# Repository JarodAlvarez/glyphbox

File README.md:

# GLYPHBOX

A 1-bit fantasy console you can build yourself. Games are written in Lua, printed as Aztec codes on credit-card-sized cards, and read by a camera in the console's card slot.

| | |
|---|---|
| Display | 128 × 128, 1-bit |
| Input | D-pad, action button, menu button |
| Audio | 2 cart channels (square, triangle, noise) + system channel |
| Sprites | 128 tiles, 8 × 8, 1-bit |
| Frame rate | 30 fps |
| Carts | Lua, up to 8 cards |

**Website:** https://jarodalvarez.github.io/glyphbox/

**Try it:** the [browser playground](https://jarodalvarez.github.io/glyphbox/playground/) runs the real console in your browser. Write Lua, draw sprites, and run.

**Learn:** [make your first game](https://jarodalvarez.github.io/glyphbox/learn/) in six lessons, with every example running on a live console. The [docs](docs/) cover the full API and the card budget.

**Make a game:** install the [devkit](devkit/) for `glyph new`, `glyph run` (live reload), `glyph build` and `glyph print`.

| Folder | What's in it |
|---|---|
| [docs/](docs/) | Lessons, API reference, cart format |
| [devkit/](devkit/) | The `glyph` command-line devkit |
| [games/](games/) | Original games, with source |
| [hardware/](hardware/) | Bill of materials. Case and controller files are coming |
| [site/](site/) | The website and playground |

## Licenses

GLYPHBOX is several things under different terms. See [LICENSE.md](LICENSE.md).

- **Devkit and example code:** MIT
- **Docs:** CC BY 4.0
- **Hardware files:** CC BY-NC-SA 4.0. Build one, modify it and share it, but don't sell it.
- **Console software:** proprietary, free to download and use
- **Name and logo:** see [TRADEMARK.md](TRADEMARK.md)

Games you make belong to you. License them however you like.

(C) Gureedo 2026

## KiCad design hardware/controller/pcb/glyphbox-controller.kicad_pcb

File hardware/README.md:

# Hardware

Everything needed to build a GLYPHBOX console and its controller. The [build guide](https://jarodalvarez.github.io/glyphbox/docs/build.html) walks through it step by step.

| Folder | What's in it |
|---|---|
| [BOM.csv](BOM.csv) | Every part, with quantities and notes |
| [case/](case/) | The console case: STLs to print, and the parametric script that makes them |
| [controller/pcb/](controller/pcb/) | The controller board: KiCad project, footprints, 3D model and Gerbers ready to order |
| [controller/firmware/](controller/firmware/) | `code.py` for the Raspberry Pi Pico (CircuitPython) |
| [controller/shell/](controller/shell/) | The printed controller shell, and the scripts that build it |

**One part you add yourself:** the controller shell's membrane mounts come from the Lensless Game Boy Pocket shell, whose licence doesn't allow sharing adaptations. The shell here is published without them, and [controller/shell/](controller/shell/) shows how to add them from your own download.

## Licence

The hardware files are licensed **CC BY-NC-SA 4.0**. You can build, modify and share them, but not sell consoles, kits or parts made from them, and changes you share must use the same licence. The GLYPHBOX name and logo are covered separately, see [TRADEMARK.md](../TRADEMARK.md).

## Credits

- The controller's membrane pad shapes are adapted from Natalie the Nerd's [YAPoco](https://github.com/nataliethenerd) Game Boy Pocket reference.
- The controller shell's membrane mounts come from the [Lensless Gameboy Pocket / Pocket Color Shell](http://pcbway.com/project/shareproject/Lensless_Gameboy_Pocket_Pocket_Color_Shell_243a0f87.html) (CC BY-NC-ND), added by each builder from their own copy.
- The controller uses reproduction Game Boy Pocket buttons and membranes.

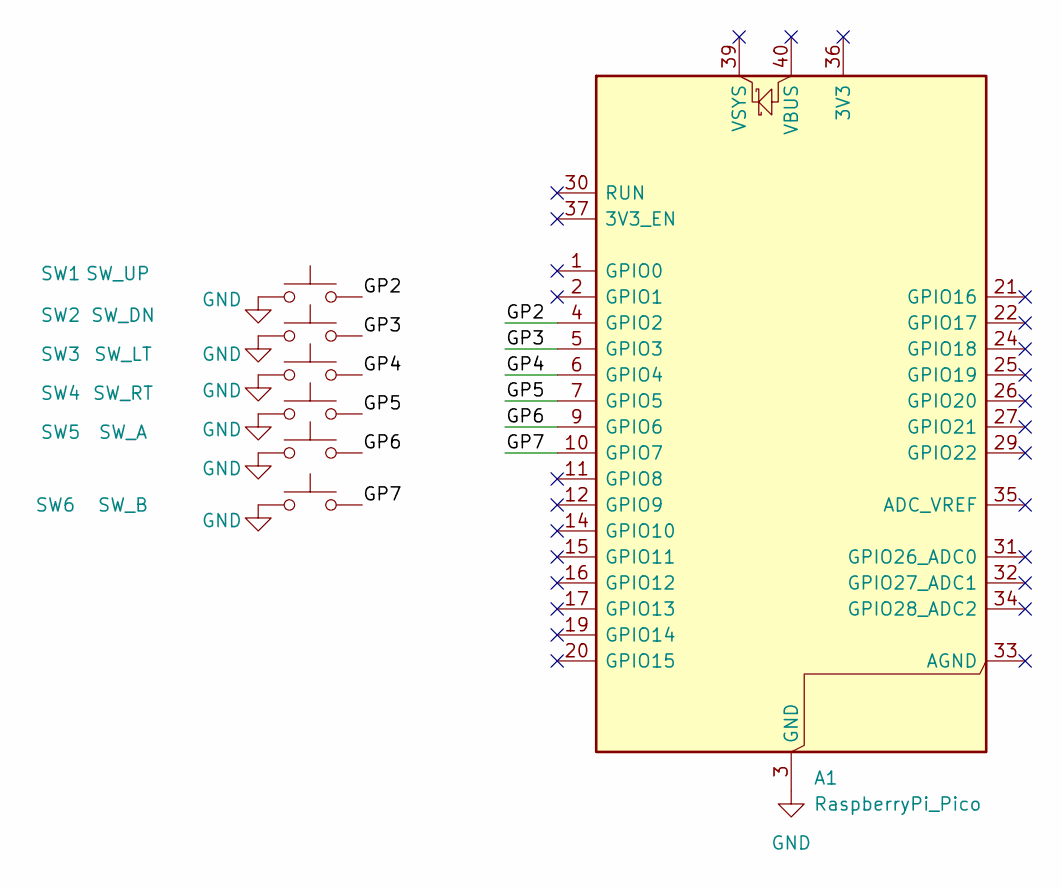
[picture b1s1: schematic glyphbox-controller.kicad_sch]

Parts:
A1: RaspberryPi_Pico; RaspberryPi_Pico_Common_Unspecified
SW1: SW_UP; GBP_Membrane_Contact
SW2: SW_DN; GBP_Membrane_Contact
SW3: SW_LT; GBP_Membrane_Contact
SW4: SW_RT; GBP_Membrane_Contact
SW5: SW_A; GBP_Membrane_Contact
SW6: SW_B; GBP_Membrane_Contact_CGB

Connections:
/GP2: A1.4 (GPIO2), SW1.2
/GP3: A1.5 (GPIO3), SW2.2
/GP4: A1.6 (GPIO4), SW3.2
/GP5: A1.7 (GPIO5), SW4.2
/GP6: A1.9 (GPIO6), SW5.2
/GP7: A1.10 (GPIO7), SW6.2
GND: A1.3 (GND), A1.8 (GND), A1.13 (GND), A1.18 (GND), A1.23 (GND), A1.28 (GND), A1.38 (GND), SW1.1, SW2.1, SW3.1, SW4.1, SW5.1, SW6.1

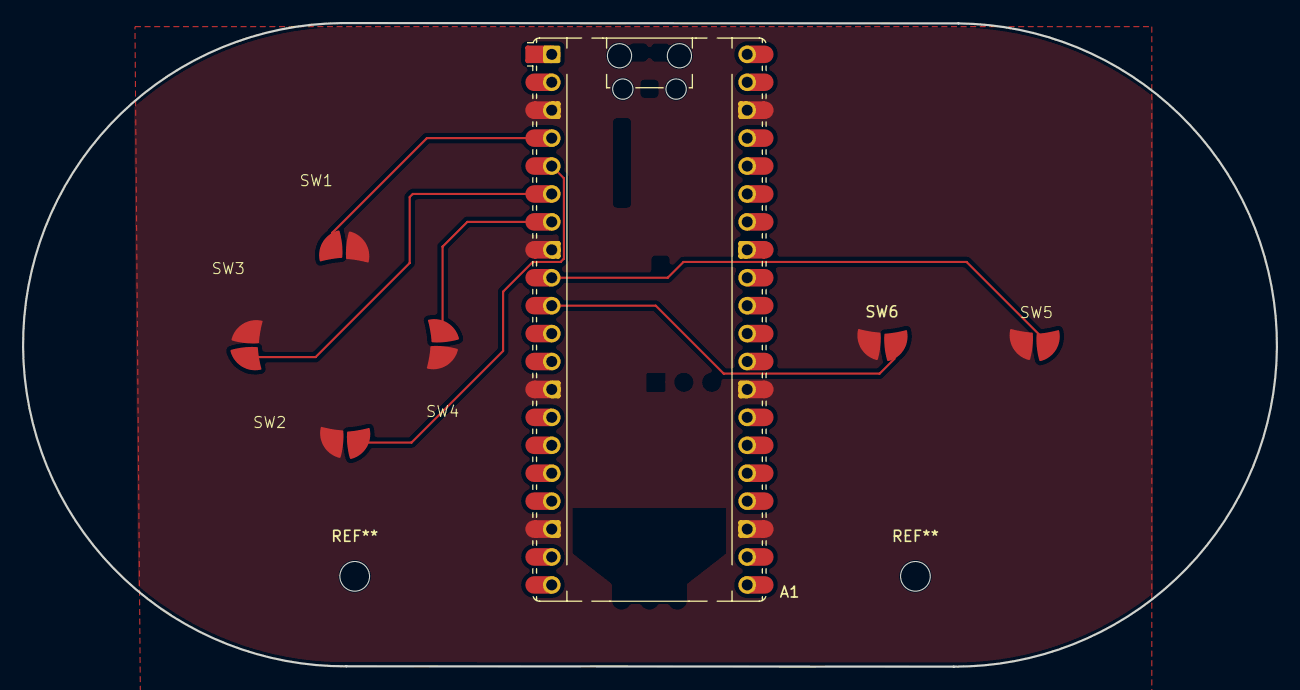
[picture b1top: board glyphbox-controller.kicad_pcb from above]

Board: 2 copper layers, 114.0 x 58.5 mm, 7 parts (0 on the bottom side), 7 nets.

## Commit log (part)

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2026-03-28 Initial commit — GLYPHBOX fantasy console
2026-03-28 Add web emulator build
2026-03-28 Fix GitHub Pages source path
2026-03-28 Show live scan attempt counter in web scanner
2026-03-28 Fix ZXing API: use BrowserMultiFormatReader with correct hints
2026-03-28 Switch to zxing-wasm (C++ ZXing) for reliable Aztec decoding
2026-04-08 Startup animation, jingle, and save dir fix
2026-05-22 Improve Pi scanning: multi-threshold, sharpening, fix cart-daemon N-card format

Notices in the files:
parts and their libraries:
GBP/GBC D-pad membrane contact. Pad geometry derived from YAPoco CGB footprint by nataliethenerd (CC BY-SA 4.0). Two custom polygon pads, ~2.25mm centre-to-centre. Carbon pill bridges both pads when pressed.
